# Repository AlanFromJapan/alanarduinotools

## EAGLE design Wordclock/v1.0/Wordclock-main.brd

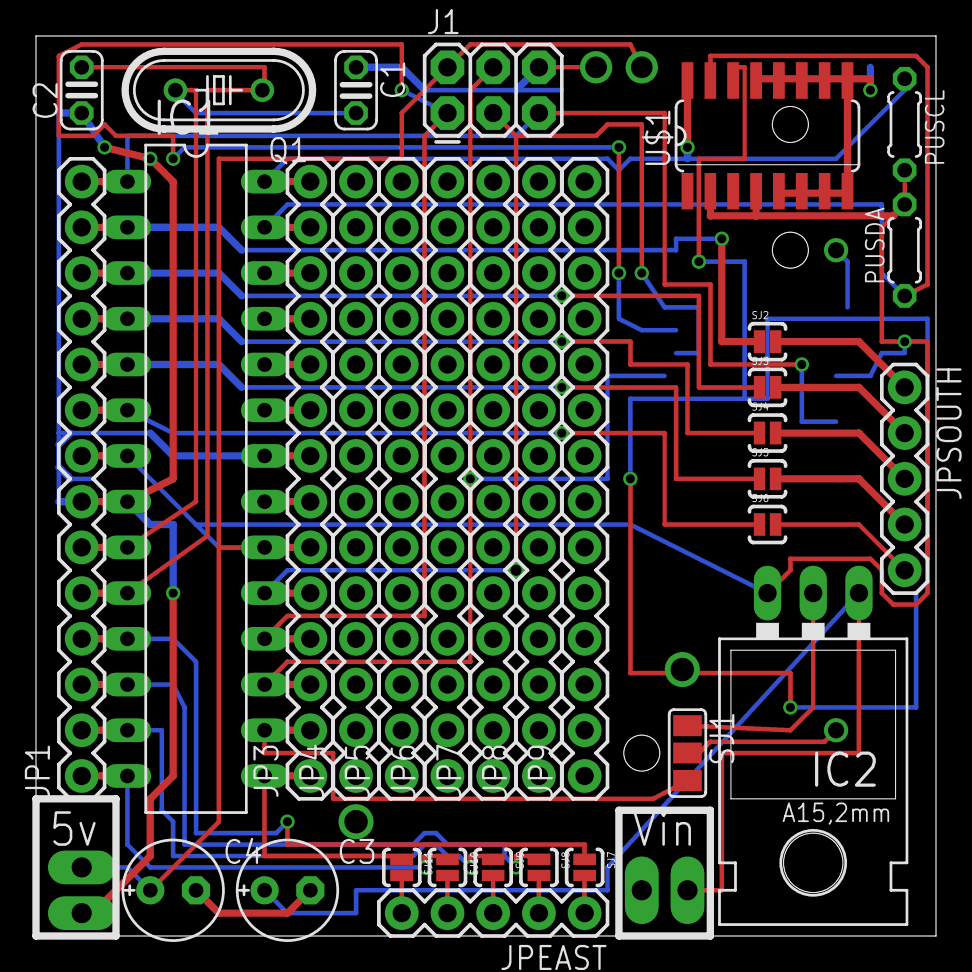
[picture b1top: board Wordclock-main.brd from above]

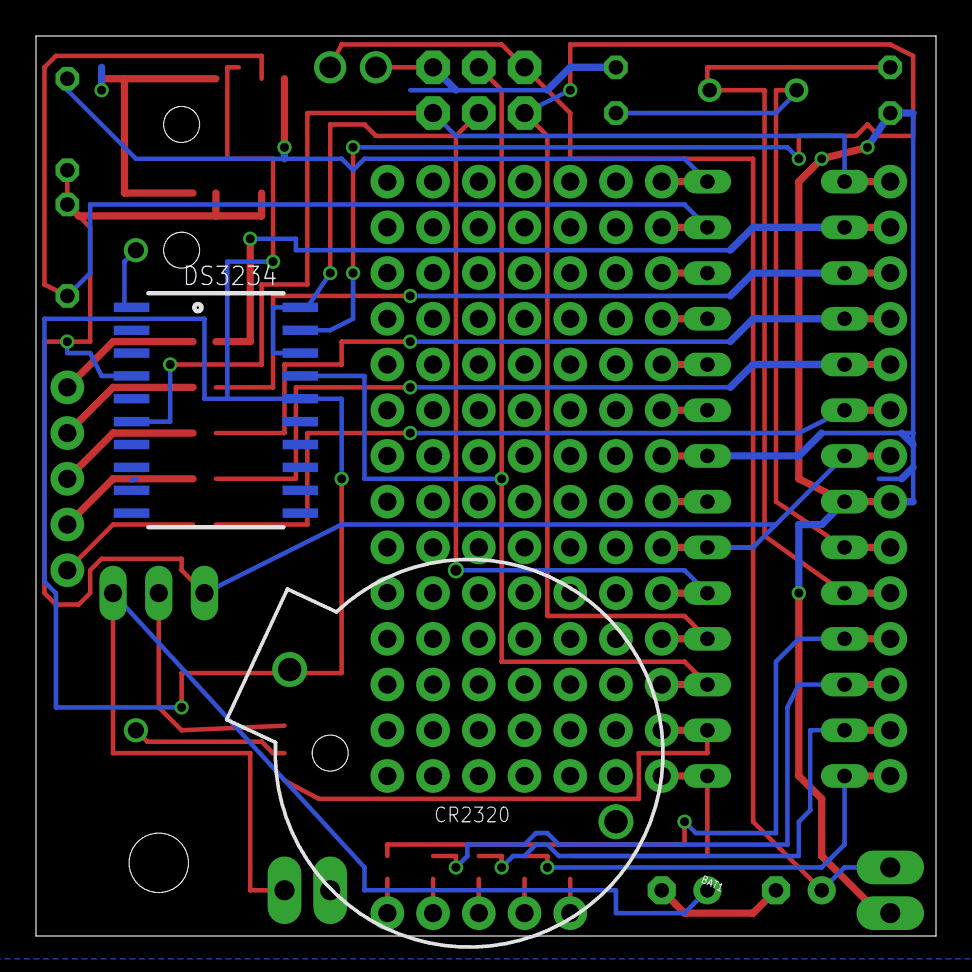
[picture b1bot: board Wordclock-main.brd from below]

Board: 2 copper layers, 50.0 x 50.0 mm, 36 parts (2 on the bottom side), 39 nets.

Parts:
5V: 1X02_LONGPADS
BAT1: BATTCOM_20MM_PTH
C1, C2: 22pF; C025-024X044
C3: 47u; E2,5-6E
C4: 4.7u; E2,5-6E
DS3234: DS3234
IC1: MEGA8-P; DIL28-3
IC2: 78XXL
J1: AVR_SPI_PRG_6PTH; 2X3
JP1, JP3, JP4, JP5, JP6, JP7, JP8, JP9: M14; 1X14
JPEAST: 1X05
JPSOUTH: 1X05
PUSCL: 10k; 0204/5
PUSDA: 10k; 0204/5
Q1: 16MHz; HC49/S
SJ1: SJ_2
SJ2, SJ3, SJ4, SJ5, SJ6, SJ7, SJ8, SJ9, SJ10, SJ11: SOLDERJUMPERNO; SJ_2S-NO
U$1: DS3231; SO16
UNREGULATED: 1X02_LONGPADS

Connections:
BATP: BAT1.1, DS3234.16, U$1.14
GND: 5V.1, BAT1.2, C1.1, C2.1, C3.-, C4.-, DS3234.2, DS3234.7, DS3234.8, DS3234.9, DS3234.10, DS3234.11, DS3234.12, DS3234.13, DS3234.14, DS3234.15, IC1.8, IC1.22, IC2.GND, J1.6, JP1.7, JP3.8, SJ1.1, U$1.5, U$1.6, U$1.7, U$1.8, U$1.9, U$1.10, U$1.11, U$1.12, U$1.13, UNREGULATED.1
unnamed: DS3234.1, SJ1.2
unnamed: JPEAST.1, SJ7.2
unnamed: C1.2, IC1.9, JP1.6, Q1.2
unnamed: C2.2, IC1.10, JP1.5, Q1.1
unnamed: IC1.16, JP3.2, SJ1.3
unnamed: JPEAST.2, SJ8.2
unnamed: JPEAST.3, SJ9.2
unnamed: JPEAST.4, SJ10.2
unnamed: JPEAST.5, SJ11.2
unnamed: DS3234.18, DS3234.20, IC1.19, J1.3, JP3.5
unnamed: DS3234.19, IC1.18, J1.1, JP3.4
unnamed: DS3234.17, IC1.17, J1.4, JP3.3
unnamed: JPSOUTH.1, SJ2.2
unnamed: JPSOUTH.2, SJ3.2
unnamed: JPSOUTH.3, SJ4.2
unnamed: JPSOUTH.4, SJ5.2
unnamed: JPSOUTH.5, SJ6.2
unnamed: IC1.2, JP1.13, SJ2.1
unnamed: IC1.3, JP1.12, SJ3.1
unnamed: IC1.4, JP1.11, SJ4.1
unnamed: IC1.5, JP1.10, SJ5.1
unnamed: IC1.6, JP1.9, SJ6.1
unnamed: IC1.15, JP3.1, SJ11.1
unnamed: IC1.14, JP1.1, SJ10.1
unnamed: IC1.13, JP1.2, SJ9.1
unnamed: IC1.12, JP1.3, SJ8.1
unnamed: IC1.11, JP1.4, SJ7.1
unnamed: IC1.28, JP3.14, PUSCL.1, U$1.16
unnamed: IC1.27, JP3.13, PUSDA.1, U$1.15
RESET: DS3234.6, IC1.1, J1.5, JP1.14
S$2: IC1.26, JP3.12
S$3: IC1.25, JP3.11
S$4: IC1.24, JP3.10
S$5: IC1.23, JP3.9
S$6: IC1.21, JP3.7
VCC: 5V.2, C4.+, DS3234.4, IC1.7, IC1.20, IC2.OUT, J1.2, JP1.8, JP3.6, PUSCL.2, PUSDA.2, U$1.2, U$1.4
VIN: C3.+, IC2.IN, UNREGULATED.2

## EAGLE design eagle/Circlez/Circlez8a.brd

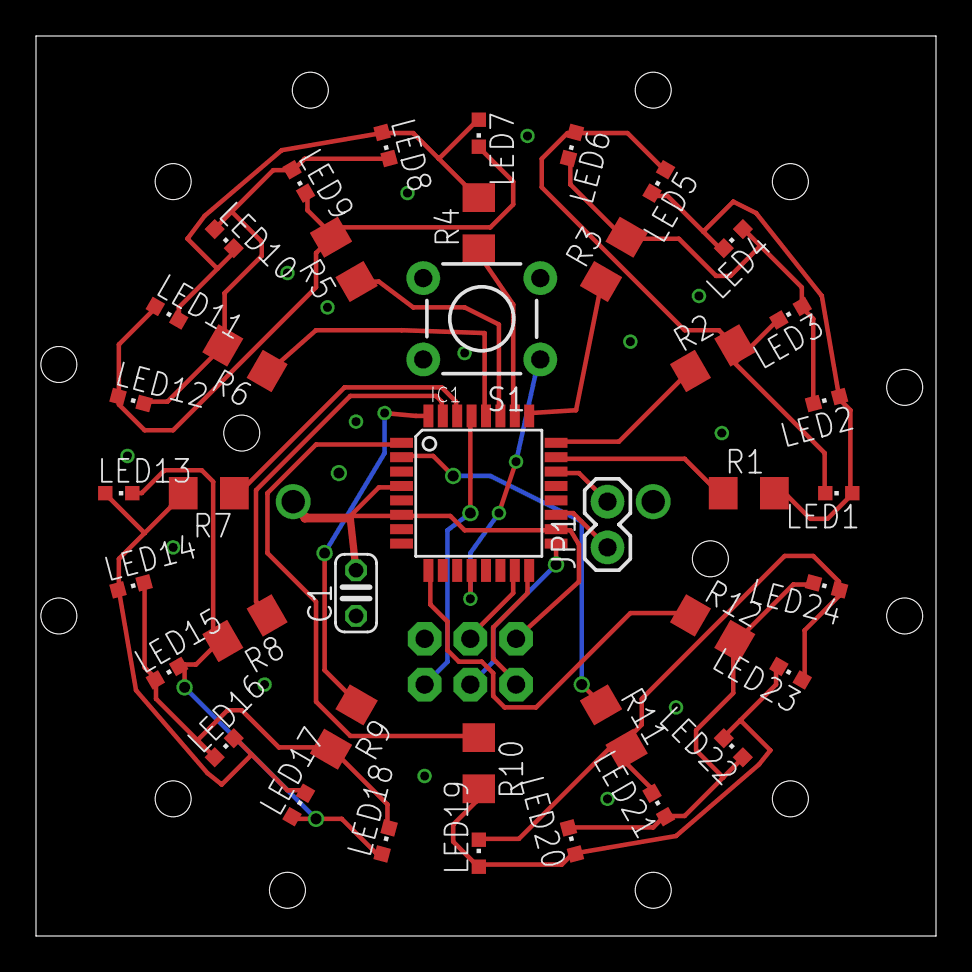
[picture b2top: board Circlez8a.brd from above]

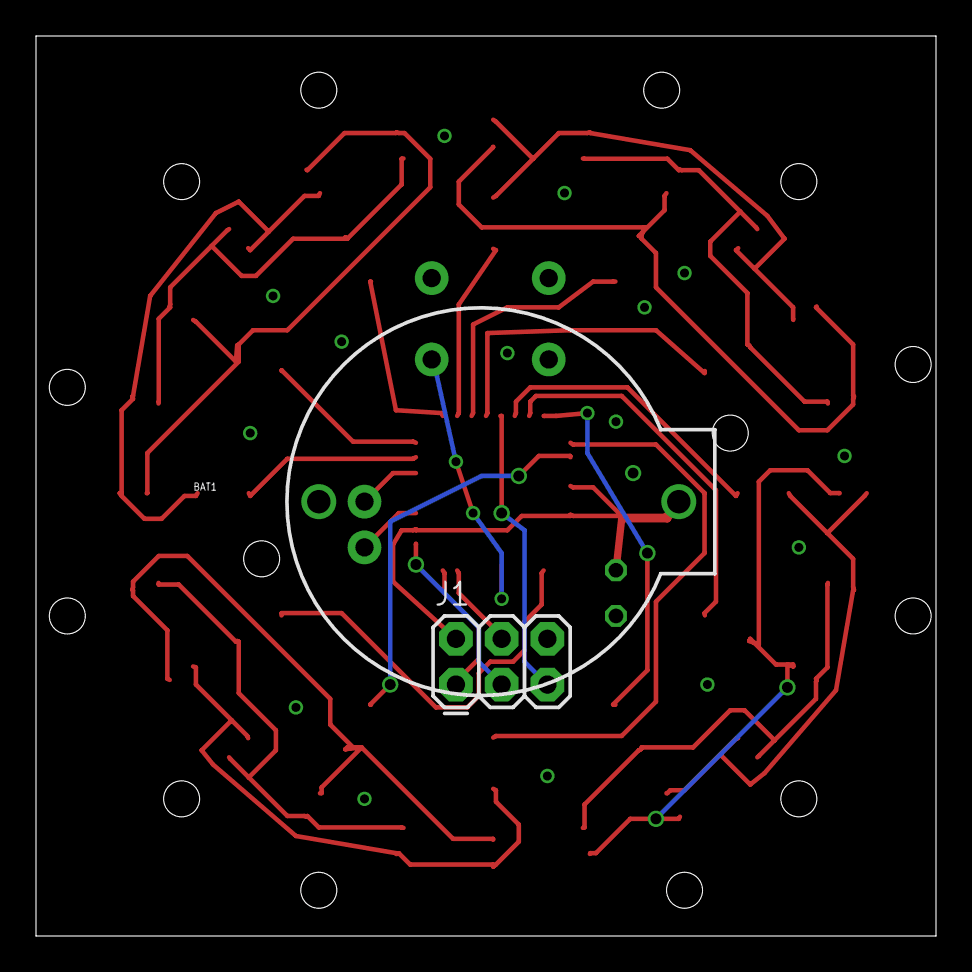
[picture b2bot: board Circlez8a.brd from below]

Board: 4 copper layers, 50.0 x 50.0 mm, 42 parts (2 on the bottom side), 33 nets.

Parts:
BAT1: BATTCOM_20MM_PTH
C1: C025-024X044
IC1: MEGA8-AI; TQFP32-08
J1: AVR_SPI_PRG_6PTH; 2X3
JP1: 1X02
LED1, LED2, LED3, LED4, LED5, LED6, LED7, LED8, LED9, LED10, LED11, LED12, LED13, LED14, LED15, LED16, LED17, LED18, LED19, LED20, LED21, LED22, LED23, LED24: CHIPLED_0603
R1, R2, R3, R4, R5, R6, R7, R8, R9, R10, R11, R12: R1206
S1: SWITCH-MOMENTARY-2PTH; TACTILE-PTH

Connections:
GND: BAT1.2, C1.1, IC1.3, IC1.5, IC1.21, J1.6, S1.3
unnamed: IC1.12, S1.1
unnamed: IC1.16, J1.1
unnamed: IC1.17, J1.3
unnamed: IC1.15, J1.4
unnamed: IC1.29, J1.5
unnamed: LED1.A, LED2.A, LED4.C, LED5.C, R1.2
unnamed: LED2.C, LED3.A, LED4.A, LED6.C, R3.2
unnamed: LED1.C, LED3.C, LED5.A, LED6.A, R2.2
unnamed: IC1.22, JP1.2
unnamed: LED7.A, LED8.A, LED10.C, LED11.C, R4.2
unnamed: LED8.C, LED9.A, LED10.A, LED12.C, R6.2
unnamed: LED7.C, LED9.C, LED11.A, LED12.A, R5.2
unnamed: LED13.A, LED14.A, LED16.C, LED17.C, R7.2
unnamed: LED14.C, LED15.A, LED16.A, LED18.C, R9.2
unnamed: LED13.C, LED15.C, LED17.A, LED18.A, R8.2
unnamed: LED19.A, LED20.A, LED22.C, LED23.C, R10.2
unnamed: LED20.C, LED21.A, LED22.A, LED24.C, R12.2
unnamed: LED19.C, LED21.C, LED23.A, LED24.A, R11.2
unnamed: IC1.23, R1.1
unnamed: IC1.24, R2.1
unnamed: IC1.25, R3.1
unnamed: IC1.26, R4.1
unnamed: IC1.27, R5.1
unnamed: IC1.28, R6.1
unnamed: IC1.30, R7.1
unnamed: IC1.31, R8.1
unnamed: IC1.32, R9.1
unnamed: IC1.1, R10.1
unnamed: IC1.2, R11.1
unnamed: IC1.9, R12.1
unnamed: IC1.19, JP1.1
VCC: BAT1.1, C1.2, IC1.4, IC1.6, IC1.18, J1.2

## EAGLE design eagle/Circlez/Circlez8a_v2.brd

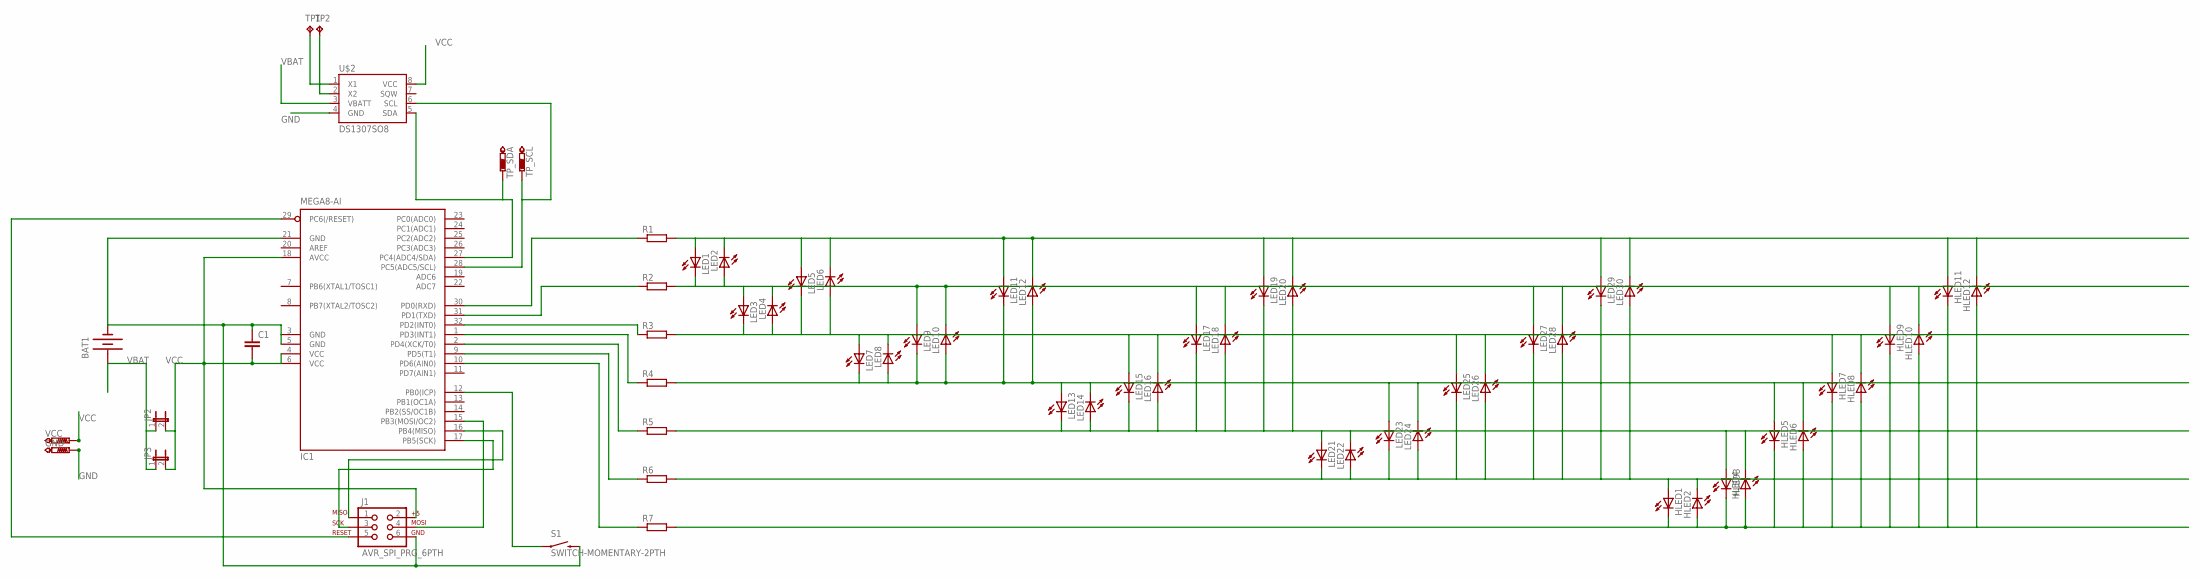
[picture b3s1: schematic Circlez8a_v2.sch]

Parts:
BAT1: BATTERY20PTH; BATTCOM_20MM_PTH
C1: C-EU025-024X044; C025-024X044
GND: PTR1TP15SQ; TP15SQ
HLED1, HLED2, HLED3, HLED4, HLED5, HLED6, HLED7, HLED8, HLED9, HLED10, HLED11, HLED12: LEDCHIP-LED0603; CHIP-LED0603
IC1: MEGA8-AI; TQFP32-08
J1: AVR_SPI_PRG_6PTH; 2X3
JP2: JUMPER-2SMD-NO; SJ_2S-NO
JP3: JUMPER-2PTH; 1X02
LED1, LED2, LED3, LED4, LED5, LED6, LED7, LED8, LED9, LED10, LED11, LED12, LED13, LED14, LED15, LED16, LED17, LED18, LED19, LED20, LED21, LED22, LED23, LED24, LED25, LED26, LED27, LED28, LED29, LED30: LEDCHIPLED_0603; CHIPLED_0603
R1, R2, R3, R4, R5, R6, R7: R-EU_R1206; R1206
S1: SWITCH-MOMENTARY-2PTH; TACTILE-PTH
TP1, TP2: TPTP13SQ; TP13SQ
TP_SCL: PTR1TP09SQ; TP09SQ
TP_SDA: PTR1TP09SQ; TP09SQ
U$2: DS1307SO8; SO08
VCC: PTR1TP15SQ; TP15SQ

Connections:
GND: BAT1.2 (-), C1.1, GND.TP, IC1.3 (GND), IC1.5 (GND), IC1.21 (GND), J1.6, S1.3 (2), U$2.4 (GND)
unnamed: IC1.12 (PB0(ICP)), S1.1
unnamed: HLED11.A, HLED12.C, LED1.A, LED2.C, LED5.A, LED6.C, LED11.A, LED12.C, LED19.A, LED20.C, LED29.A, LED30.C, R1.2
unnamed: IC1.16 (PB4(MISO)), J1.1
unnamed: IC1.17 (PB5(SCK)), J1.3
unnamed: IC1.15 (PB3(MOSI/OC2)), J1.4
unnamed: IC1.29 (PC6(/RESET)), J1.5
unnamed: HLED9.A, HLED10.C, LED1.C, LED2.A, LED3.A, LED4.C, LED9.A, LED10.C, LED17.A, LED18.C, LED27.A, LED28.C, R2.2
unnamed: HLED5.A, HLED6.C, LED7.C, LED8.A, LED9.C, LED10.A, LED11.C, LED12.A, LED13.A, LED14.C, LED23.A, LED24.C, R4.2
unnamed: HLED3.A, HLED4.C, LED13.C, LED14.A, LED15.C, LED16.A, LED17.C, LED18.A, LED19.C, LED20.A, LED21.A, LED22.C, R5.2
unnamed: IC1.28 (PC5(ADC5/SCL)), TP_SCL.TP, U$2.6 (SCL)
unnamed: HLED1.A, HLED2.C, LED21.C, LED22.A, LED23.C, LED24.A, LED25.C, LED26.A, LED27.C, LED28.A, LED29.C, LED30.A, R6.2
unnamed: HLED1.C, HLED2.A, HLED3.C, HLED4.A, HLED5.C, HLED6.A, HLED7.C, HLED8.A, HLED9.C, HLED10.A, HLED11.C, HLED12.A, R7.2
unnamed: IC1.30 (PD0(RXD)), R1.1
unnamed: IC1.31 (PD1(TXD)), R2.1
unnamed: IC1.32 (PD2(INT0)), R3.1
unnamed: IC1.1 (PD3(INT1)), R4.1
unnamed: IC1.2 (PD4(XCK/T0)), R5.1
unnamed: IC1.9 (PD5(T1)), R6.1
unnamed: IC1.10 (PD6(AIN0)), R7.1
unnamed: TP1.TP, U$2.1 (X1)
unnamed: TP2.TP, U$2.2 (X2)
unnamed: IC1.27 (PC4(ADC4/SDA)), TP_SDA.TP, U$2.5 (SDA)
unnamed: HLED7.A, HLED8.C, LED3.C, LED4.A, LED5.C, LED6.A, LED7.A, LED8.C, LED15.A, LED16.C, LED25.A, LED26.C, R3.2
VBAT: BAT1.1 (+), JP2.1, JP3.1, U$2.3 (VBATT)
VCC: C1.2, IC1.4 (VCC), IC1.6 (VCC), IC1.18 (AVCC), J1.2, JP2.2, JP3.2, U$2.8 (VCC), VCC.TP

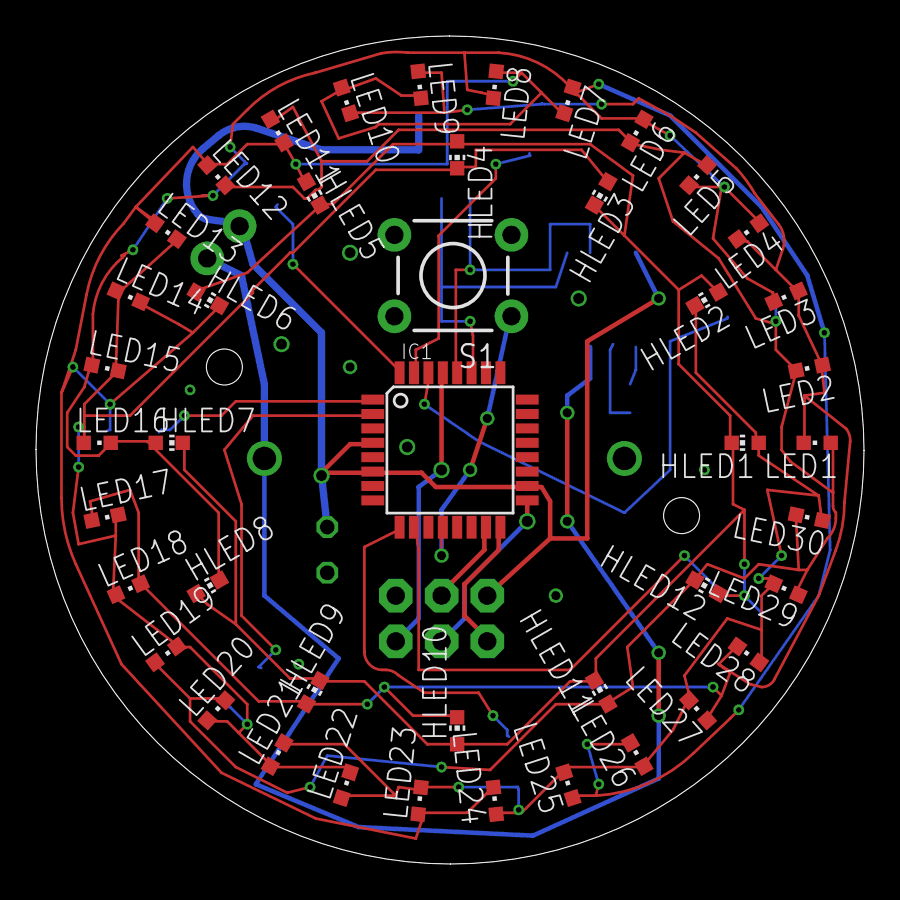
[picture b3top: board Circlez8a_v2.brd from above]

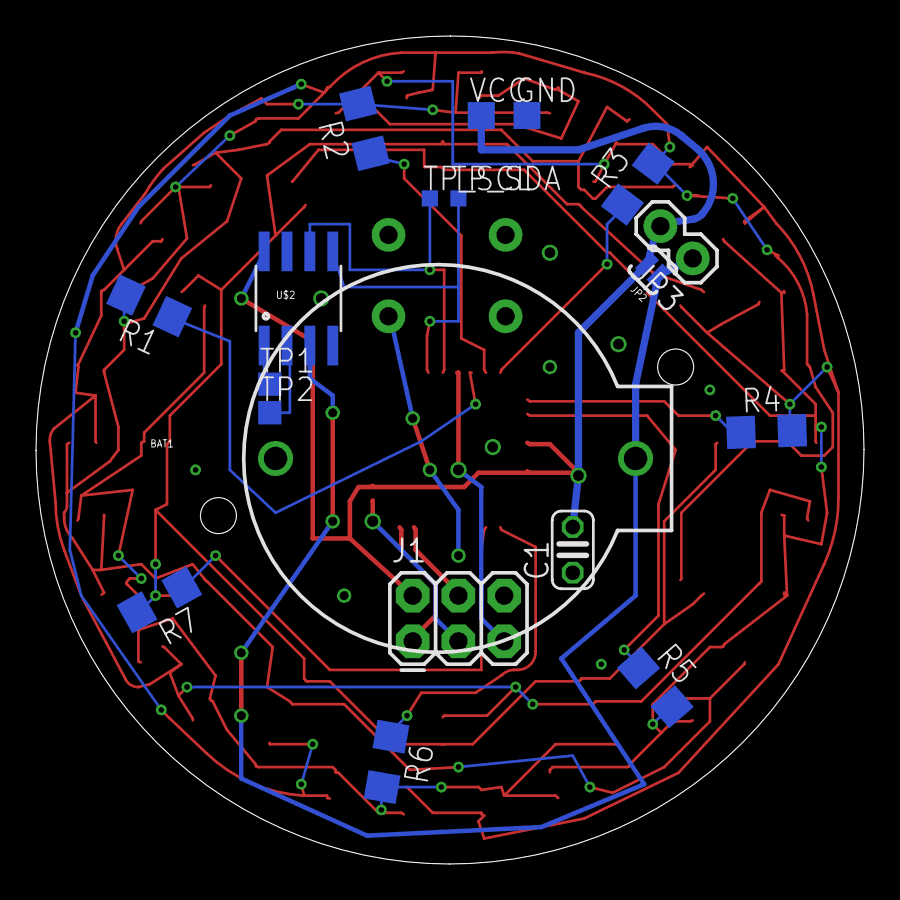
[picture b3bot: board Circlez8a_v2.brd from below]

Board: 4 copper layers, 46.0 x 46.0 mm, 63 parts (19 on the bottom side), 26 nets.

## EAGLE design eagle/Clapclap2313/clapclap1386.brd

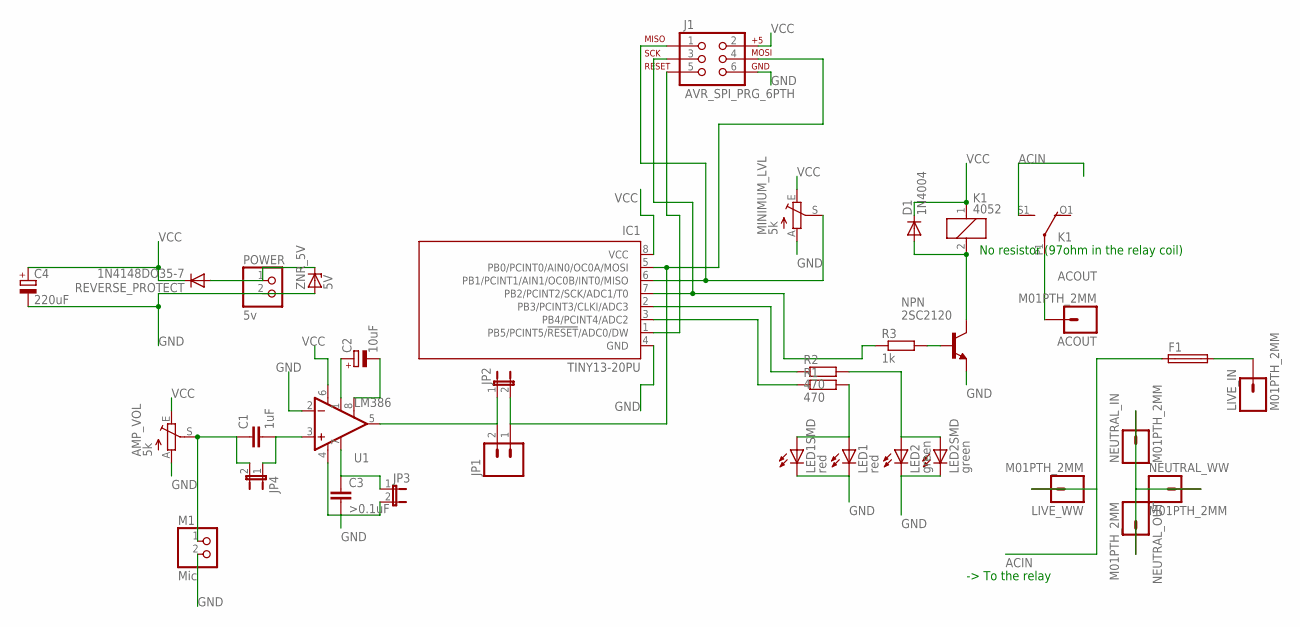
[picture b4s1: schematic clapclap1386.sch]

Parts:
ACOUT: M01PTH_2MM; 1X01_2MM
AMP_VOL: 5k; CT6
C1: 1uF; C050-024X044
C2: 10uF; E2,5-6E
C3: >0.1uF; C025-025X050
C4: 220uF; E2,5-6E
D1: 1N4004; DO41-10
F1: TE5
IC1: TINY13-20PU; DIL08
J1: AVR_SPI_PRG_6PTH; 2X3
JP1: M02PTH; 1X02
JP2, JP3, JP4: JUMPER-2SMD-NO; SJ_2S-NO
K1: 4052; F4052
LED1: red; LED3MM
LED1SMD: red; KA-3528ASYC
LED2: green; LED3MM
LED2SMD: green; KA-3528ASYC
LIVE_IN: M01PTH_2MM; 1X01_2MM
LIVE_WW: M01PTH_2MM; 1X01_2MM
M1: Mic; 1X02
MINIMUM_LVL: 5k; CT6
NEUTRAL_IN: M01PTH_2MM; 1X01_2MM
NEUTRAL_OUT: M01PTH_2MM; 1X01_2MM
NEUTRAL_WW: M01PTH_2MM; 1X01_2MM
NPN: 2SC2120; TO92-ECB
POWER: 5v; 1X02
R1, R2: 470; 0204V
R3: 1k; 0207/2V
REVERSE_PROTECT: 1N4148DO35-7; DO35-7
U1: LM386; DIP08
ZNR_5V: 5V; ZDIO-2.5

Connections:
ACIN: F1.1, K1.S1 (S), LIVE_WW.1
ACOUT: ACOUT.1, K1.P1
GND: AMP_VOL.A, C3.2, C4.-, IC1.4 (GND), J1.6, JP3.2, LED1.K (C), LED1SMD.C, LED2.K (C), LED2SMD.C, M1.2, MINIMUM_LVL.A, NPN.E, POWER.2, U1.2 (-IN), U1.4 (V-), ZNR_5V.A
unnamed: C1.2, JP4.1, U1.3 (+IN)
unnamed: IC1.7 (PB2/PCINT2/SCK/ADC1/T0), J1.3, R3.1
unnamed: AMP_VOL.S, C1.1, JP4.2, M1.1
unnamed: IC1.2 (PB3/PCINT3/CLKI/ADC3), R2.1
unnamed: C2.+, U1.1 (GAIN)
unnamed: IC1.3 (PB4/PCINT4/ADC2), R1.1
unnamed: LED1.A, LED1SMD.A, R1.2
unnamed: NPN.B, R3.2
unnamed: D1.A, K1.2, NPN.C
unnamed: IC1.5 (PB0/PCINT0/AIN0/OC0A/MOSI), J1.4, JP1.1, JP2.2
unnamed: LED2.A, LED2SMD.A, R2.2
unnamed: IC1.6 (PB1/PCINT1/AIN1/OC0B/INT0/MISO), J1.1, MINIMUM_LVL.S
unnamed: NEUTRAL_IN.1, NEUTRAL_OUT.1, NEUTRAL_WW.1
unnamed: C2.-, U1.8 (GAIN)
unnamed: C3.1, JP3.1, U1.7 (BP)
unnamed: IC1.1 (PB5/PCINT5/!RESET!/ADC0/DW), J1.5
unnamed: JP1.2, JP2.1, U1.5 (OUT)
unnamed: POWER.1, REVERSE_PROTECT.A, ZNR_5V.C
unnamed: F1.2, LIVE_IN.1
VCC: AMP_VOL.E, C4.+, D1.C, IC1.8 (VCC), J1.2, K1.1, MINIMUM_LVL.E, REVERSE_PROTECT.C, U1.6 (V+)

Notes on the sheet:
No resistor (97ohm in the relay coil)
-> To the relay

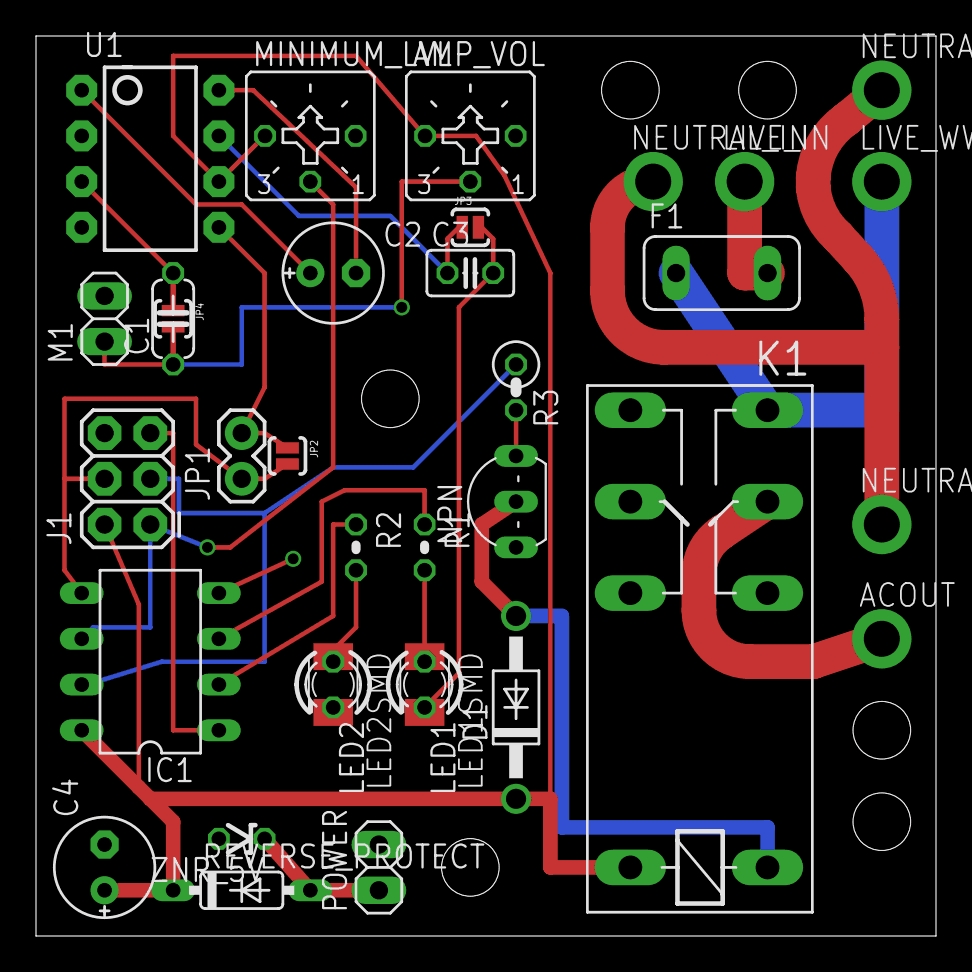
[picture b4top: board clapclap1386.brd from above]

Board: 4 copper layers, 50.0 x 50.0 mm, 34 parts (0 on the bottom side), 23 nets.

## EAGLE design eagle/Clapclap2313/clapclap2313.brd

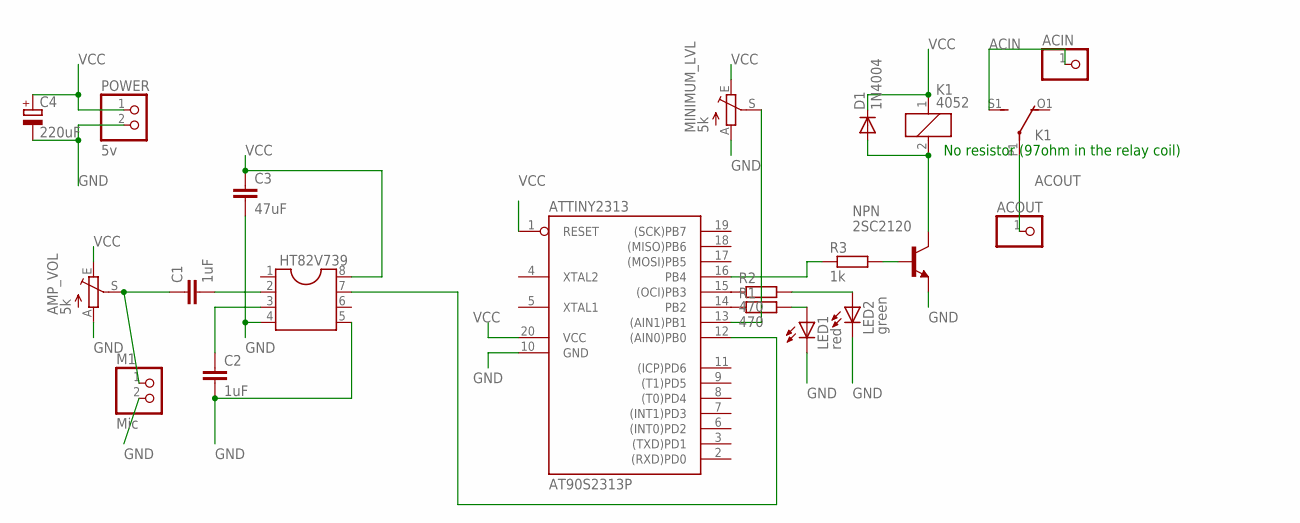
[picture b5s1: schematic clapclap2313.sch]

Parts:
ACIN: PINHD-1X1; 1X01
ACOUT: PINHD-1X1; 1X01
AMP_VOL: 5k; CT6
ATTINY2313: AT90S2313P; DIL20
C1, C2: 1uF; C050-024X044
C3: 47uF; C050-024X044
C4: 220uF; E2,5-6E
D1: 1N4004; DO41-10
HT82V739: DIL8S; SOCKET-08
K1: 4052; F4052
LED1: red; LED3MM
LED2: green; LED3MM
M1: Mic; 1X02
MINIMUM_LVL: 5k; CT6
NPN: 2SC2120; TO92-ECB
POWER: 5v; 1X02
R1, R2: 470; 0204V
R3: 1k; 0207/2V

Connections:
ACIN: ACIN.1, K1.S1 (S)
ACOUT: ACOUT.1, K1.P1
GND: AMP_VOL.A, ATTINY2313.10 (GND), C2.2, C3.2, C4.-, HT82V739.4, HT82V739.5, LED1.K (C), LED2.K (C), M1.2, MINIMUM_LVL.A, NPN.E, POWER.2
unnamed: C2.1, HT82V739.3
unnamed: ATTINY2313.16 (PB4), R3.1
unnamed: AMP_VOL.S, C1.1, M1.1
unnamed: ATTINY2313.14 (PB2), R1.1
unnamed: C1.2, HT82V739.2
unnamed: ATTINY2313.15 ((OCI)PB3), R2.1
unnamed: LED1.A, R1.2
unnamed: NPN.B, R3.2
unnamed: D1.A, K1.2, NPN.C
unnamed: ATTINY2313.12 ((AIN0)PB0), HT82V739.7
unnamed: LED2.A, R2.2
unnamed: ATTINY2313.13 ((AIN1)PB1), MINIMUM_LVL.S
VCC: AMP_VOL.E, ATTINY2313.1 (RESET), ATTINY2313.20 (VCC), C3.1, C4.+, D1.C, HT82V739.8, K1.1, MINIMUM_LVL.E, POWER.1

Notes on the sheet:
No resistor (97ohm in the relay coil)

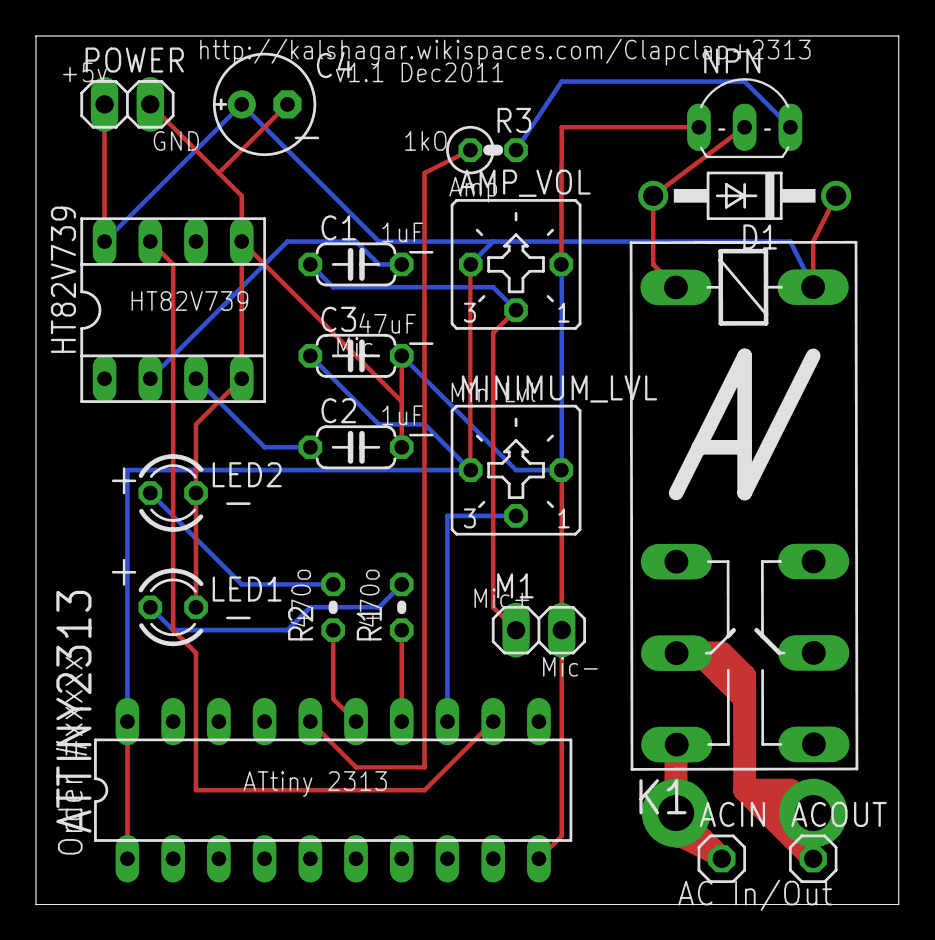
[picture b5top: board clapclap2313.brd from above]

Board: 2 copper layers, 47.9 x 48.2 mm, 20 parts (0 on the bottom side), 16 nets.

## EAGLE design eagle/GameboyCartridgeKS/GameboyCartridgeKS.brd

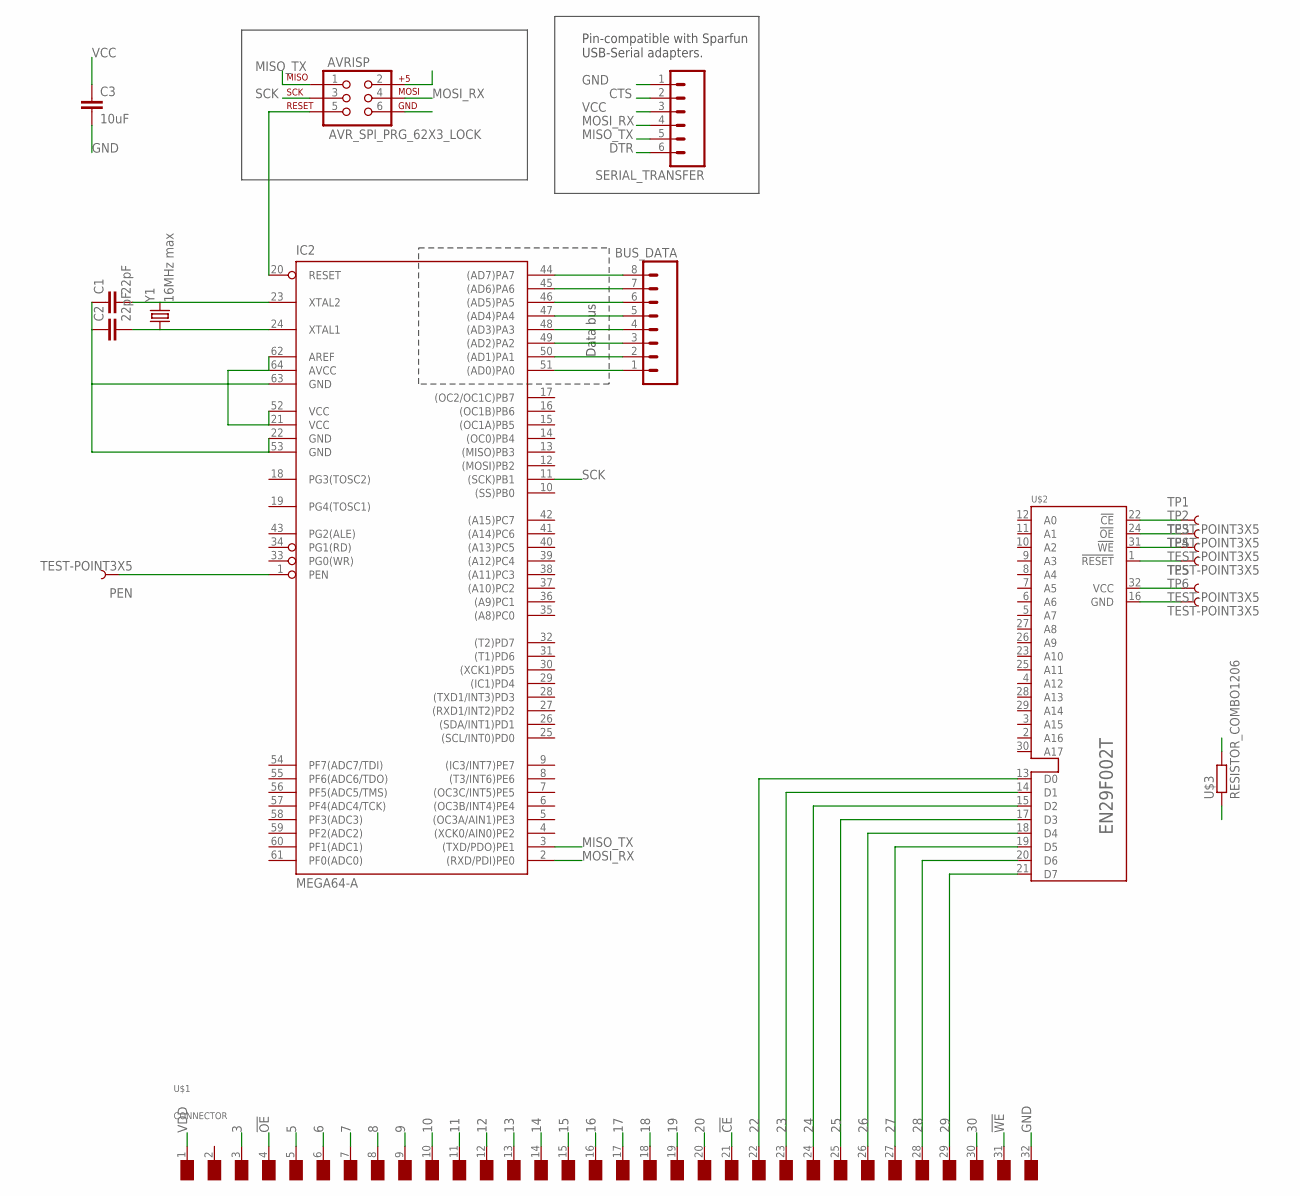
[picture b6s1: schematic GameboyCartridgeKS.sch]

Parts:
AVRISP: AVR_SPI_PRG_62X3_LOCK; 2X3_LOCK
BUS_DATA: M08NO_SILK; 1X08_PIN1_NO_SILK
C1, C2: 22pF; C0805K
C3: 10uF; C1206K
IC2: MEGA64-A; TQFP64
PEN: TEST-POINT3X5; PAD.03X.05
SERIAL_TRANSFER: M06SILK_FEMALE_PTH; 1X06
TP1, TP2, TP3, TP4, TP5, TP6: TEST-POINT3X5; PAD.03X.05
U$1: CONNECTOR
U$2: EN29F002T; PLCC-S32
U$3: RESISTOR_COMBO1206; 207-10_SMD_COMBO
Y1: 16MHz max; HC49U-V

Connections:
3: U$1.3 (/WR)
5: U$1.5 (/RCS)
6: U$1.6 (A0)
7: U$1.7 (A1)
8: U$1.8 (A2)
9: U$1.9 (A3)
10: U$1.10 (A4)
11: U$1.11 (A5)
12: U$1.12 (A6)
13: U$1.13 (A7)
14: U$1.14 (A8)
15: U$1.15 (A9)
16: U$1.16 (A10)
17: U$1.17 (A11)
18: U$1.18 (A12)
19: U$1.19 (A13)
20: U$1.20 (A14)
22: BUS_DATA.1, IC2.51 ((AD0)PA0), U$1.22 (D0), U$2.13 (D0)
23: BUS_DATA.2, IC2.50 ((AD1)PA1), U$1.23 (D1), U$2.14 (D1)
24: BUS_DATA.3, IC2.49 ((AD2)PA2), U$1.24 (D2), U$2.15 (D2)
25: BUS_DATA.4, IC2.48 ((AD3)PA3), U$1.25 (D3), U$2.17 (D3)
26: BUS_DATA.5, IC2.47 ((AD4)PA4), U$1.26 (D4), U$2.18 (D4)
27: BUS_DATA.6, IC2.46 ((AD5)PA5), U$1.27 (D5), U$2.19 (D5)
28: BUS_DATA.7, IC2.45 ((AD6)PA6), U$1.28 (D6), U$2.20 (D6)
29: BUS_DATA.8, IC2.44 ((AD7)PA7), U$1.29 (D7), U$2.21 (D7)
30: U$1.30 (/RS)
!CE: TP1.P$1, U$1.21 (A15), U$2.22 (!CE)
!OE: TP2.P$1, U$1.4 (/RD), U$2.24 (!OE)
!RESET: TP4.P$1, U$2.1 (!RESET)
!WE: TP3.P$1, U$1.31 (VIN), U$2.31 (!WE), U$3.1, U$3.4 (1)
CTS: SERIAL_TRANSFER.2
DTR: SERIAL_TRANSFER.6
GND: AVRISP.6, C1.1, C2.1, C3.2, IC2.22 (GND), IC2.53 (GND), IC2.63 (GND), SERIAL_TRANSFER.1, TP6.P$1, U$1.32 (GND), U$2.16 (GND)
MISO_TX: AVRISP.1, IC2.3 ((TXD/PDO)PE1), SERIAL_TRANSFER.5
MOSI_RX: AVRISP.4, IC2.2 ((RXD/PDI)PE0), SERIAL_TRANSFER.4
unnamed: C1.2, IC2.23 (XTAL2), Y1.2
unnamed: AVRISP.5, IC2.20 (RESET)
unnamed: C2.2, IC2.24 (XTAL1), Y1.1
PEN: IC2.1 (PEN), PEN.P$1
SCK: AVRISP.3, IC2.11 ((SCK)PB1)
VCC: AVRISP.2, C3.1, IC2.21 (VCC), IC2.52 (VCC), IC2.62 (AREF), IC2.64 (AVCC), SERIAL_TRANSFER.3, TP5.P$1, U$2.32 (VCC), U$3.2, U$3.3 (2)
VDD: U$1.1 (VDD)

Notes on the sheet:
Pin-compatible with Sparfun USB-Serial adapters.
Data bus

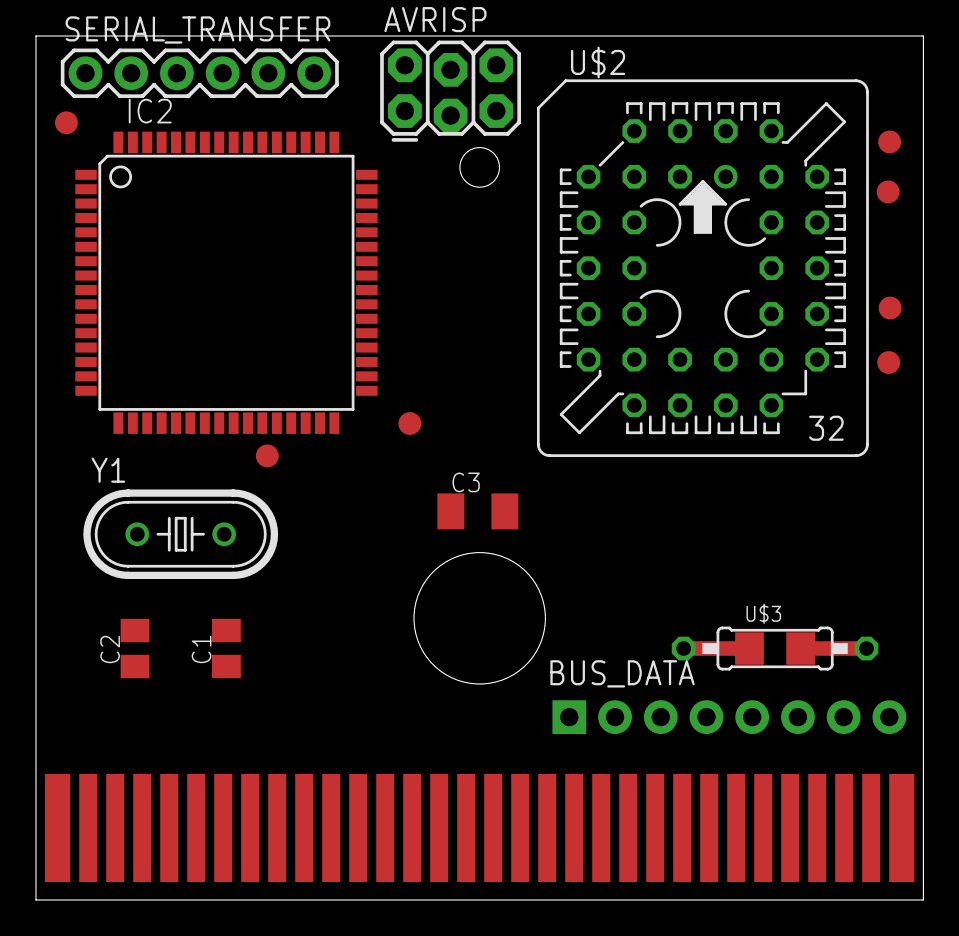
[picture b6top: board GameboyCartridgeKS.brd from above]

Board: 2 copper layers, 49.3 x 48.0 mm, 18 parts (0 on the bottom side), 21 nets.

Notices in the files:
parts and their libraries:
SparkFun: Licensing: CC v3.0 Share-Alike You are welcome to use this library for commercial purposes.
SparkFun-Connectors: Licensing: Creative Commons ShareAlike 4.0 International - https://creativecommons.org/licenses/by-sa/4.0
